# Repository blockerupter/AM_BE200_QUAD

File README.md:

AM_BE200_QUAD
=============

BE200 Board with 4 chips

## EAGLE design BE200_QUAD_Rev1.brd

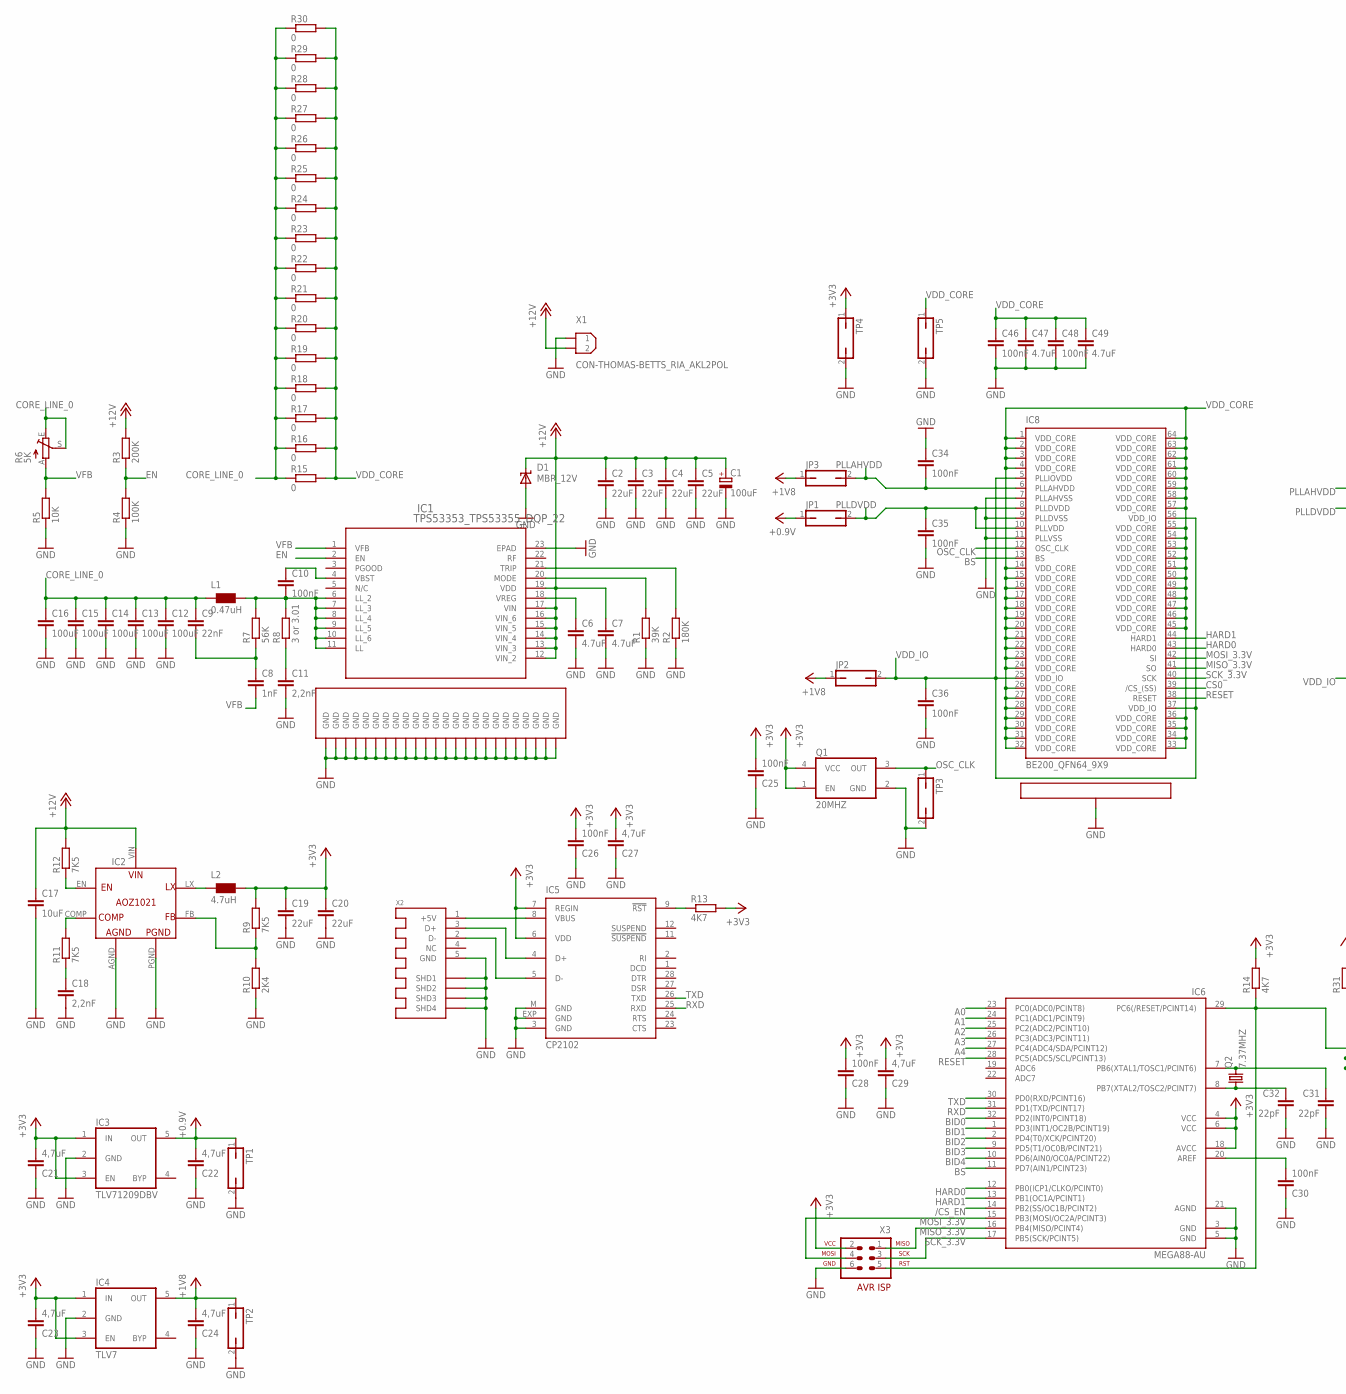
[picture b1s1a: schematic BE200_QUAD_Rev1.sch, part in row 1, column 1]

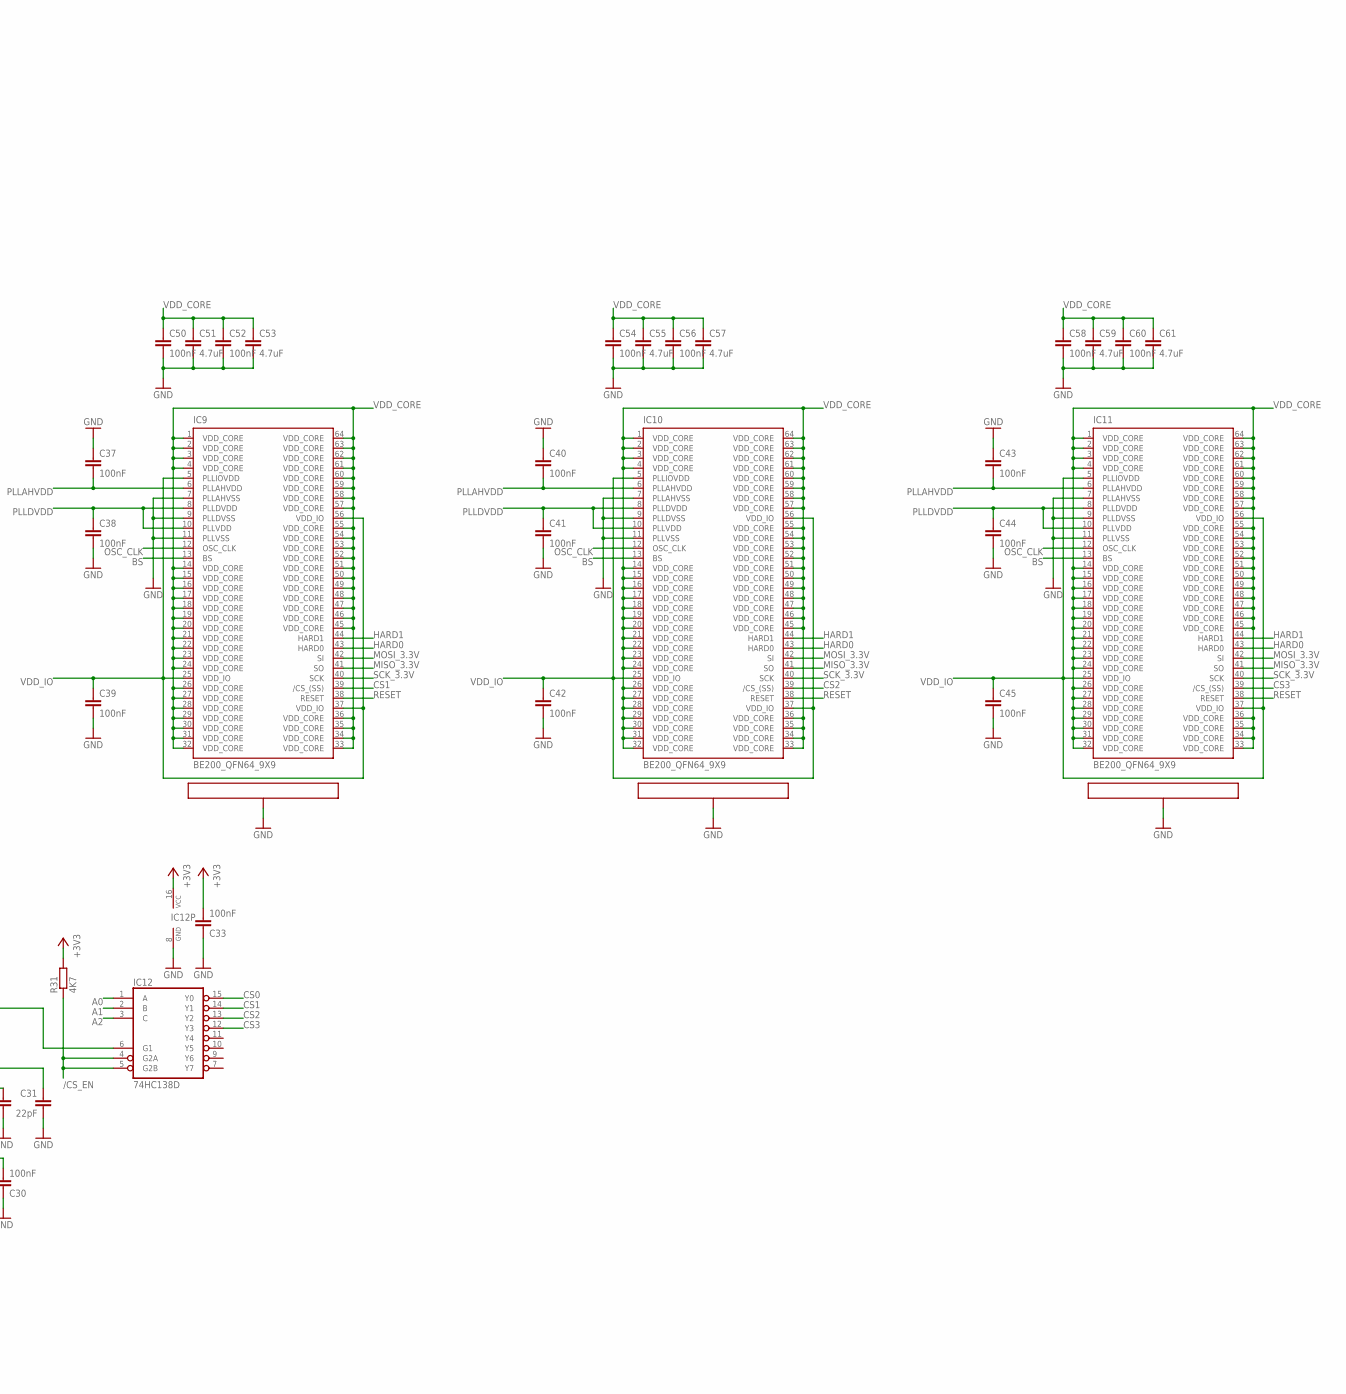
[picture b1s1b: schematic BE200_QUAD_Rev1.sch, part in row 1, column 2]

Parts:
C1: 100uF; 153CLV-0605
C2, C3, C4, C5: 22uF; C1210K
C6, C7: 4.7uF; C0805K
C8: 1nF; C0805K
C9: 22nF; C0805K
C10, C25, C26, C28, C30, C33: 100nF; C0805K
C11, C18: 2,2nF; C0805K
C12, C13, C14, C15, C16: 100uF; C1210K
C17: 10uF; C1206K
C19, C20: 22uF; C1206K
C21, C22, C23, C24, C27, C29: 4,7uF; C0805K
C31, C32: 22pF; C0805K
C34, C35, C36, C37, C38, C39, C40, C41, C42, C43, C44, C45, C46, C48, C50, C52, C54, C56, C58, C60: 100nF; MYRCL_C0603K
C47, C49, C51, C53, C55, C57, C59, C61: 4.7uF; MYRCL_C0603K
D1: MBR_12V; SMBJ
IC1: TPS53353_TPS53355_DQP_22; DQP22_5P479X3P24
IC2: AOZ1021
IC3: TLV71209DBV; SOT-23-5
IC4: TLV7; SOT-23-5
IC5: CP2102; SILABS2_MLP28
IC6: MEGA88-AU; TQFP32-08
IC8, IC9, IC10, IC11: BE200_QFN64_9X9; QFN64-9X9
IC12: 74HC138D; SO16
JP1, JP2, JP3: JP1Q; JP1
L1: 0.47uH; INDUCTOR_PA0513
L2: 4.7uH; INDCUCTOR_7.3X7.3
Q1: 20MHZ; OSCILLATOR_7X5_SMD
Q2: 7.37MHZ; HC49UP
R1: 39K; R0805K
R2: 180K; R0805K
R3: 200K; R0805K
R4: 100K; R0805K
R5: 10K; R0805K
R6: 5K; S64W
R7: 56K; R0805K
R8: 3 or 3.01; R0805K
R9, R11, R12: 7K5; R0805K
R10: 2K4; R0805K
R13, R14, R31: 4K7; R0805K
R15, R16, R17, R18, R19, R20, R21, R22, R23, R24, R25, R26, R27, R28, R29, R30: 0; R0805K
TP1, TP2, TP3, TP4, TP5: JP1Q; JP1
X1: CON-THOMAS-BETTS_RIA_AKL2POL
X2: MYSTUFF_USB-MINI-ASSMANN; MYSTUFF_USB_MINI-ASSMANN
X3: AVR-ISP-6VERT; AVR-ISP-6

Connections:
+0.9V: C22.2, IC3.5 (OUT), JP1.1, TP1.1
+1V8: C24.2, IC4.5 (OUT), JP2.1, JP3.1, TP2.1
+3V3: C19.1, C20.1, C21.2, C23.2, C25.2, C26.2, C27.2, C28.2, C29.2, C33.2, IC3.1 (IN), IC3.3 (EN), IC4.1 (IN), IC4.3 (EN), IC5.6 (VDD), IC5.7 (REGIN), IC6.4 (VCC), IC6.6 (VCC), IC6.18 (AVCC), IC12.16 (VCC), L2.2, Q1.1 (EN), Q1.4 (VCC), R9.2, R13.2, R14.2, R31.2, TP4.1, X3.2
+12V: C1.+, C2.1, C3.1, C4.1, C5.1, C7.1, C17.1, D1.C, IC1.12 (VIN_2), IC1.13 (VIN_3), IC1.14 (VIN_4), IC1.15 (VIN_5), IC1.16 (VIN_6), IC1.17 (VIN), IC1.19 (VDD), IC2.VIN, R3.2, R12.2, X1.2
/CS_EN: IC6.14 (PB2(SS/OC1B/PCINT2)), IC12.4 (G2A), IC12.5 (G2B), R31.1
A0: IC6.23 (PC0(ADC0/PCINT8)), IC12.1 (A)
A1: IC6.24 (PC1(ADC1/PCINT9)), IC12.2 (B)
A2: IC6.25 (PC2(ADC2/PCINT10)), IC12.3 (C)
A3: IC6.26 (PC3(ADC3/PCINT11))
A4: IC6.27 (PC4(ADC4/SDA/PCINT12))
BID0: IC6.32 (PD2(INT0/PCINT18))
BID1: IC6.1 (PD3(INT1/OC2B/PCINT19))
BID2: IC6.2 (PD4(T0/XCK/PCINT20))
BID3: IC6.9 (PD5(T1/OC0B/PCINT21))
BID4: IC6.10 (PD6(AIN0/OC0A/PCINT22))
BS: IC6.11 (PD7(AIN1/PCINT23)), IC8.13 (BS), IC9.13 (BS), IC10.13 (BS), IC11.13 (BS)
CORE_LINE_0: C9.1, C12.1, C13.1, C14.1, C15.1, C16.1, L1.1, R6.E, R6.S, R15.1, R16.1, R17.1, R18.1, R19.1, R20.1, R21.1, R22.1, R23.1, R24.1, R25.1, R26.1, R27.1, R28.1, R29.1, R30.1
CS0: IC8.39 (/CS_(SS)), IC12.15 (Y0)
CS1: IC9.39 (/CS_(SS)), IC12.14 (Y1)
CS2: IC10.39 (/CS_(SS)), IC12.13 (Y2)
CS3: IC11.39 (/CS_(SS)), IC12.12 (Y3)
EN: IC1.2 (EN), R3.1, R4.2
GND: C1.-, C2.2, C3.2, C4.2, C5.2, C6.2, C7.2, C11.2, C12.2, C13.2, C14.2, C15.2, C16.2, C17.2, C18.2, C19.2, C20.2, C21.1, C22.1, C23.1, C24.1, C25.1, C26.1, C27.1, C28.1, C29.1, C30.1, C31.2, C32.2, C33.1, C34.1, C35.2, C36.2, C37.1, C38.2, C39.2, C40.1, C41.2, C42.2, C43.1, C44.2, C45.2, C46.2, C47.2, C48.2, C49.2, C50.2, C51.2, C52.2, C53.2, C54.2, C55.2, C56.2, C57.2, C58.2, C59.2, C60.2, C61.2, D1.A, IC1.23 (EPAD), IC1.GND@1 (GND), IC1.GND@2 (GND), IC1.GND@3 (GND), IC1.GND@4 (GND), IC1.GND@5 (GND), IC1.GND@6 (GND), IC1.GND@7 (GND), IC1.GND@8 (GND), IC1.GND@9 (GND), IC1.GND@10 (GND), IC1.GND@11 (GND), IC1.GND@12 (GND), IC1.GND@13 (GND), IC1.GND@14 (GND), IC1.GND@15 (GND), IC1.GND@16 (GND), IC1.GND@17 (GND), IC1.GND@18 (GND), IC1.GND@19 (GND), IC1.GND@20 (GND), IC1.GND@21 (GND), IC1.GND@22 (GND), IC1.GND@23 (GND), IC1.GND@24 (GND), IC2.AGND, IC2.PGND, IC3.2 (GND), IC4.2 (GND), IC5.3 (GND), IC5.EXP (GND), IC5.M (GND), IC6.3 (GND), IC6.5 (GND), IC6.21 (AGND), IC8.7 (PLLAHVSS), IC8.9 (PLLDVSS), IC8.11 (PLLVSS), IC8.EXP@1 (GND), IC8.EXP@2 (GND), IC8.EXP@3 (GND), IC8.EXP@4 (GND), IC8.EXP@5 (GND), IC8.EXP@6 (GND), IC8.EXP@7 (GND), IC8.EXP@8 (GND), IC8.EXP@9 (GND), IC8.EXP@10 (GND), IC8.EXP@11 (GND), IC8.EXP@12 (GND), IC8.EXP@13 (GND), IC8.EXP@14 (GND), IC8.EXP@15 (GND), IC8.EXP@16 (GND), IC8.EXP@17 (GND), IC8.EXP@18 (GND), IC8.EXP@19 (GND), IC8.EXP@20 (GND), IC8.EXP@21 (GND), IC8.EXP@22 (GND), IC8.EXP@23 (GND), IC8.EXP@24 (GND), IC8.EXP@25 (GND), IC8.EXP@26 (GND), IC8.EXP@27 (GND), IC8.EXP@28 (GND), IC8.EXP@29 (GND), IC8.EXP@30 (GND), IC8.EXP@31 (GND), IC8.EXP@32 (GND), IC8.EXP@33 (GND), IC8.EXP@34 (GND), IC8.EXP@35 (GND), IC8.EXP@36 (GND), IC8.EXP@37 (GND), IC8.EXP@38 (GND), IC8.EXP@39 (GND), IC8.EXP@40 (GND), IC8.EXP@41 (GND), IC8.EXP@42 (GND), IC8.EXP@43 (GND), IC8.EXP@44 (GND), IC8.EXP@45 (GND), IC8.EXP@46 (GND), IC8.EXP@47 (GND), IC8.EXP@48 (GND), IC8.EXP@49 (GND), IC9.7 (PLLAHVSS), IC9.9 (PLLDVSS), IC9.11 (PLLVSS), IC9.EXP@1 (GND), IC9.EXP@2 (GND), IC9.EXP@3 (GND), IC9.EXP@4 (GND), IC9.EXP@5 (GND), IC9.EXP@6 (GND), IC9.EXP@7 (GND), IC9.EXP@8 (GND), IC9.EXP@9 (GND), IC9.EXP@10 (GND), IC9.EXP@11 (GND), IC9.EXP@12 (GND), IC9.EXP@13 (GND), IC9.EXP@14 (GND), IC9.EXP@15 (GND), IC9.EXP@16 (GND), IC9.EXP@17 (GND), IC9.EXP@18 (GND), IC9.EXP@19 (GND), IC9.EXP@20 (GND), IC9.EXP@21 (GND), IC9.EXP@22 (GND), IC9.EXP@23 (GND), IC9.EXP@24 (GND), IC9.EXP@25 (GND), IC9.EXP@26 (GND), IC9.EXP@27 (GND), IC9.EXP@28 (GND), IC9.EXP@29 (GND), IC9.EXP@30 (GND), IC9.EXP@31 (GND), IC9.EXP@32 (GND), IC9.EXP@33 (GND), IC9.EXP@34 (GND), IC9.EXP@35 (GND), IC9.EXP@36 (GND), IC9.EXP@37 (GND), IC9.EXP@38 (GND), IC9.EXP@39 (GND), IC9.EXP@40 (GND), IC9.EXP@41 (GND), IC9.EXP@42 (GND), IC9.EXP@43 (GND), IC9.EXP@44 (GND), IC9.EXP@45 (GND), IC9.EXP@46 (GND), IC9.EXP@47 (GND), IC9.EXP@48 (GND), IC9.EXP@49 (GND), IC10.7 (PLLAHVSS), IC10.9 (PLLDVSS), IC10.11 (PLLVSS), IC10.EXP@1 (GND), IC10.EXP@2 (GND), IC10.EXP@3 (GND), IC10.EXP@4 (GND), IC10.EXP@5 (GND), IC10.EXP@6 (GND), IC10.EXP@7 (GND), IC10.EXP@8 (GND), IC10.EXP@9 (GND), IC10.EXP@10 (GND), IC10.EXP@11 (GND), IC10.EXP@12 (GND), IC10.EXP@13 (GND), IC10.EXP@14 (GND), IC10.EXP@15 (GND), IC10.EXP@16 (GND), IC10.EXP@17 (GND), IC10.EXP@18 (GND), IC10.EXP@19 (GND), IC10.EXP@20 (GND), IC10.EXP@21 (GND), IC10.EXP@22 (GND), IC10.EXP@23 (GND), IC10.EXP@24 (GND), IC10.EXP@25 (GND), IC10.EXP@26 (GND), IC10.EXP@27 (GND), IC10.EXP@28 (GND), IC10.EXP@29 (GND), IC10.EXP@30 (GND), IC10.EXP@31 (GND), IC10.EXP@32 (GND), IC10.EXP@33 (GND), IC10.EXP@34 (GND), IC10.EXP@35 (GND), IC10.EXP@36 (GND), IC10.EXP@37 (GND), IC10.EXP@38 (GND), IC10.EXP@39 (GND), IC10.EXP@40 (GND), IC10.EXP@41 (GND), IC10.EXP@42 (GND), IC10.EXP@43 (GND), IC10.EXP@44 (GND), IC10.EXP@45 (GND), IC10.EXP@46 (GND), IC10.EXP@47 (GND), IC10.EXP@48 (GND), IC10.EXP@49 (GND), IC11.7 (PLLAHVSS), IC11.9 (PLLDVSS), IC11.11 (PLLVSS), IC11.EXP@1 (GND), IC11.EXP@2 (GND), IC11.EXP@3 (GND), IC11.EXP@4 (GND), IC11.EXP@5 (GND), IC11.EXP@6 (GND), IC11.EXP@7 (GND), IC11.EXP@8 (GND), IC11.EXP@9 (GND), IC11.EXP@10 (GND), IC11.EXP@11 (GND), IC11.EXP@12 (GND), IC11.EXP@13 (GND), IC11.EXP@14 (GND), IC11.EXP@15 (GND), IC11.EXP@16 (GND), IC11.EXP@17 (GND), IC11.EXP@18 (GND), IC11.EXP@19 (GND), IC11.EXP@20 (GND), IC11.EXP@21 (GND), IC11.EXP@22 (GND), IC11.EXP@23 (GND), IC11.EXP@24 (GND), IC11.EXP@25 (GND), IC11.EXP@26 (GND), IC11.EXP@27 (GND), IC11.EXP@28 (GND), IC11.EXP@29 (GND), IC11.EXP@30 (GND), IC11.EXP@31 (GND), IC11.EXP@32 (GND), IC11.EXP@33 (GND), IC11.EXP@34 (GND), IC11.EXP@35 (GND), IC11.EXP@36 (GND), IC11.EXP@37 (GND), IC11.EXP@38 (GND), IC11.EXP@39 (GND), IC11.EXP@40 (GND), IC11.EXP@41 (GND), IC11.EXP@42 (GND), IC11.EXP@43 (GND), IC11.EXP@44 (GND), IC11.EXP@45 (GND), IC11.EXP@46 (GND), IC11.EXP@47 (GND), IC11.EXP@48 (GND), IC11.EXP@49 (GND), IC12.8 (GND), Q1.2 (GND), R1.1, R2.1, R4.1, R5.1, R10.1, TP1.2, TP2.2, TP3.2, TP4.2, TP5.2, X1.1, X2.5 (GND), X2.SHD1, X2.SHD2, X2.SHD3, X2.SHD4, X3.6
HARD0: IC6.12 (PB0(ICP1/CLKO/PCINT0)), IC8.43 (HARD0), IC9.43 (HARD0), IC10.43 (HARD0), IC11.43 (HARD0)
HARD1: IC6.13 (PB1(OC1A/PCINT1)), IC8.44 (HARD1), IC9.44 (HARD1), IC10.44 (HARD1), IC11.44 (HARD1)
MISO_3.3V: IC6.16 (PB4(MISO/PCINT4)), IC8.41 (SO), IC9.41 (SO), IC10.41 (SO), IC11.41 (SO), X3.1
MOSI_3.3V: IC6.15 (PB3(MOSI/OC2A/PCINT3)), IC8.42 (SI), IC9.42 (SI), IC10.42 (SI), IC11.42 (SI), X3.4
unnamed: C10.2, IC1.6 (LL_2), IC1.7 (LL_3), IC1.8 (LL_4), IC1.9 (LL_5), IC1.10 (LL_6), IC1.11 (LL), L1.2, R7.2, R8.2
unnamed: C11.1, R8.1
unnamed: C8.1, C9.2, R7.1
unnamed: IC6.29 (PC6(/RESET/PCINT14)), IC12.6 (G1), R14.1, X3.5
unnamed: IC1.21 (TRIP), R2.2
unnamed: IC1.20 (MODE), R1.2
unnamed: C6.1, IC1.18 (VREG)
unnamed: C10.1, IC1.4 (VBST)
unnamed: C18.1, R11.1
unnamed: IC2.LX, L2.1
unnamed: IC2.FB, R9.1, R10.2
unnamed: IC2.COMP, R11.2
unnamed: IC2.EN, R12.1
unnamed: C30.2, IC6.20 (AREF)
unnamed: C31.1, IC6.7 (PB6(XTAL1/TOSC1/PCINT6)), Q2.2
unnamed: IC5.9 (!RST), R13.1
unnamed: C32.1, IC6.8 (PB7(XTAL2/TOSC2/PCINT7)), Q2.1
unnamed: IC5.4 (D+), X2.3 (D+)
unnamed: IC5.5 (D-), X2.2 (D-)
unnamed: IC5.8 (VBUS), X2.1 (+5V)
OSC_CLK: IC8.12 (OSC_CLK), IC9.12 (OSC_CLK), IC10.12 (OSC_CLK), IC11.12 (OSC_CLK), Q1.3 (OUT), TP3.1
PLLAHVDD: C34.2, C37.2, C40.2, C43.2, IC8.6 (PLLAHVDD), IC9.6 (PLLAHVDD), IC10.6 (PLLAHVDD), IC11.6 (PLLAHVDD), JP3.2
PLLDVDD: C35.1, C38.1, C41.1, C44.1, IC8.8 (PLLDVDD), IC8.10 (PLLVDD), IC9.8 (PLLDVDD), IC9.10 (PLLVDD), IC10.8 (PLLDVDD), IC10.10 (PLLVDD), IC11.8 (PLLDVDD), IC11.10 (PLLVDD), JP1.2
RESET: IC6.28 (PC5(ADC5/SCL/PCINT13)), IC8.38 (RESET), IC9.38 (RESET), IC10.38 (RESET), IC11.38 (RESET)
RXD: IC5.25 (RXD), IC6.31 (PD1(TXD/PCINT17))
SCK_3.3V: IC6.17 (PB5(SCK/PCINT5)), IC8.40 (SCK), IC9.40 (SCK), IC10.40 (SCK), IC11.40 (SCK), X3.3
TXD: IC5.26 (TXD), IC6.30 (PD0(RXD/PCINT16))
VDD_CORE: C46.1, C47.1, C48.1, C49.1, C50.1, C51.1, C52.1, C53.1, C54.1, C55.1, C56.1, C57.1, C58.1, C59.1, C60.1, C61.1, IC8.1 (VDD_CORE), IC8.2 (VDD_CORE), IC8.3 (VDD_CORE), IC8.4 (VDD_CORE), IC8.14 (VDD_CORE), IC8.15 (VDD_CORE), IC8.16 (VDD_CORE), IC8.17 (VDD_CORE), IC8.18 (VDD_CORE), IC8.19 (VDD_CORE), IC8.20 (VDD_CORE), IC8.21 (VDD_CORE), IC8.22 (VDD_CORE), IC8.23 (VDD_CORE), IC8.24 (VDD_CORE), IC8.26 (VDD_CORE), IC8.27 (VDD_CORE), IC8.28 (VDD_CORE), IC8.29 (VDD_CORE), IC8.30 (VDD_CORE), IC8.31 (VDD_CORE), IC8.32 (VDD_CORE), IC8.33 (VDD_CORE), IC8.34 (VDD_CORE), IC8.35 (VDD_CORE), IC8.36 (VDD_CORE), IC8.45 (VDD_CORE), IC8.46 (VDD_CORE), IC8.47 (VDD_CORE), IC8.48 (VDD_CORE), IC8.49 (VDD_CORE), IC8.50 (VDD_CORE), IC8.51 (VDD_CORE), IC8.52 (VDD_CORE), IC8.53 (VDD_CORE), IC8.54 (VDD_CORE), IC8.55 (VDD_CORE), IC8.57 (VDD_CORE), IC8.58 (VDD_CORE), IC8.59 (VDD_CORE), IC8.60 (VDD_CORE), IC8.61 (VDD_CORE), IC8.62 (VDD_CORE), IC8.63 (VDD_CORE), IC8.64 (VDD_CORE), IC9.1 (VDD_CORE), IC9.2 (VDD_CORE), IC9.3 (VDD_CORE), IC9.4 (VDD_CORE), IC9.14 (VDD_CORE), IC9.15 (VDD_CORE), IC9.16 (VDD_CORE), IC9.17 (VDD_CORE), IC9.18 (VDD_CORE), IC9.19 (VDD_CORE), IC9.20 (VDD_CORE), IC9.21 (VDD_CORE), IC9.22 (VDD_CORE), IC9.23 (VDD_CORE), IC9.24 (VDD_CORE), IC9.26 (VDD_CORE), IC9.27 (VDD_CORE), IC9.28 (VDD_CORE), IC9.29 (VDD_CORE), IC9.30 (VDD_CORE), IC9.31 (VDD_CORE), IC9.32 (VDD_CORE), IC9.33 (VDD_CORE), IC9.34 (VDD_CORE), IC9.35 (VDD_CORE), IC9.36 (VDD_CORE), IC9.45 (VDD_CORE), IC9.46 (VDD_CORE), IC9.47 (VDD_CORE), IC9.48 (VDD_CORE), IC9.49 (VDD_CORE), IC9.50 (VDD_CORE), IC9.51 (VDD_CORE), IC9.52 (VDD_CORE), IC9.53 (VDD_CORE), IC9.54 (VDD_CORE), IC9.55 (VDD_CORE), IC9.57 (VDD_CORE), IC9.58 (VDD_CORE), IC9.59 (VDD_CORE), IC9.60 (VDD_CORE), IC9.61 (VDD_CORE), IC9.62 (VDD_CORE), IC9.63 (VDD_CORE), IC9.64 (VDD_CORE), IC10.1 (VDD_CORE), IC10.2 (VDD_CORE), IC10.3 (VDD_CORE), IC10.4 (VDD_CORE), IC10.14 (VDD_CORE), IC10.15 (VDD_CORE), IC10.16 (VDD_CORE), IC10.17 (VDD_CORE), IC10.18 (VDD_CORE), IC10.19 (VDD_CORE), IC10.20 (VDD_CORE), IC10.21 (VDD_CORE), IC10.22 (VDD_CORE), IC10.23 (VDD_CORE), IC10.24 (VDD_CORE), IC10.26 (VDD_CORE), IC10.27 (VDD_CORE), IC10.28 (VDD_CORE), IC10.29 (VDD_CORE), IC10.30 (VDD_CORE), IC10.31 (VDD_CORE), IC10.32 (VDD_CORE), IC10.33 (VDD_CORE), IC10.34 (VDD_CORE), IC10.35 (VDD_CORE), IC10.36 (VDD_CORE), IC10.45 (VDD_CORE), IC10.46 (VDD_CORE), IC10.47 (VDD_CORE), IC10.48 (VDD_CORE), IC10.49 (VDD_CORE), IC10.50 (VDD_CORE), IC10.51 (VDD_CORE), IC10.52 (VDD_CORE), IC10.53 (VDD_CORE), IC10.54 (VDD_CORE), IC10.55 (VDD_CORE), IC10.57 (VDD_CORE), IC10.58 (VDD_CORE), IC10.59 (VDD_CORE), IC10.60 (VDD_CORE), IC10.61 (VDD_CORE), IC10.62 (VDD_CORE), IC10.63 (VDD_CORE), IC10.64 (VDD_CORE), IC11.1 (VDD_CORE), IC11.2 (VDD_CORE), IC11.3 (VDD_CORE), IC11.4 (VDD_CORE), IC11.14 (VDD_CORE), IC11.15 (VDD_CORE), IC11.16 (VDD_CORE), IC11.17 (VDD_CORE), IC11.18 (VDD_CORE), IC11.19 (VDD_CORE), IC11.20 (VDD_CORE), IC11.21 (VDD_CORE), IC11.22 (VDD_CORE), IC11.23 (VDD_CORE), IC11.24 (VDD_CORE), IC11.26 (VDD_CORE), IC11.27 (VDD_CORE), IC11.28 (VDD_CORE), IC11.29 (VDD_CORE), IC11.30 (VDD_CORE), IC11.31 (VDD_CORE), IC11.32 (VDD_CORE), IC11.33 (VDD_CORE), IC11.34 (VDD_CORE), IC11.35 (VDD_CORE), IC11.36 (VDD_CORE), IC11.45 (VDD_CORE), IC11.46 (VDD_CORE), IC11.47 (VDD_CORE), IC11.48 (VDD_CORE), IC11.49 (VDD_CORE), IC11.50 (VDD_CORE), IC11.51 (VDD_CORE), IC11.52 (VDD_CORE), IC11.53 (VDD_CORE), IC11.54 (VDD_CORE), IC11.55 (VDD_CORE), IC11.57 (VDD_CORE), IC11.58 (VDD_CORE), IC11.59 (VDD_CORE), IC11.60 (VDD_CORE), IC11.61 (VDD_CORE), IC11.62 (VDD_CORE), IC11.63 (VDD_CORE), IC11.64 (VDD_CORE), R15.2, R16.2, R17.2, R18.2, R19.2, R20.2, R21.2, R22.2, R23.2, R24.2, R25.2, R26.2, R27.2, R28.2, R29.2, R30.2, TP5.1
VDD_IO: C36.1, C39.1, C42.1, C45.1, IC8.5 (PLLIOVDD), IC8.25 (VDD_IO), IC8.37 (VDD_IO), IC8.56 (VDD_IO), IC9.5 (PLLIOVDD), IC9.25 (VDD_IO), IC9.37 (VDD_IO), IC9.56 (VDD_IO), IC10.5 (PLLIOVDD), IC10.25 (VDD_IO), IC10.37 (VDD_IO), IC10.56 (VDD_IO), IC11.5 (PLLIOVDD), IC11.25 (VDD_IO), IC11.37 (VDD_IO), IC11.56 (VDD_IO), JP2.2
VFB: C8.2, IC1.1 (VFB), R5.2, R6.A

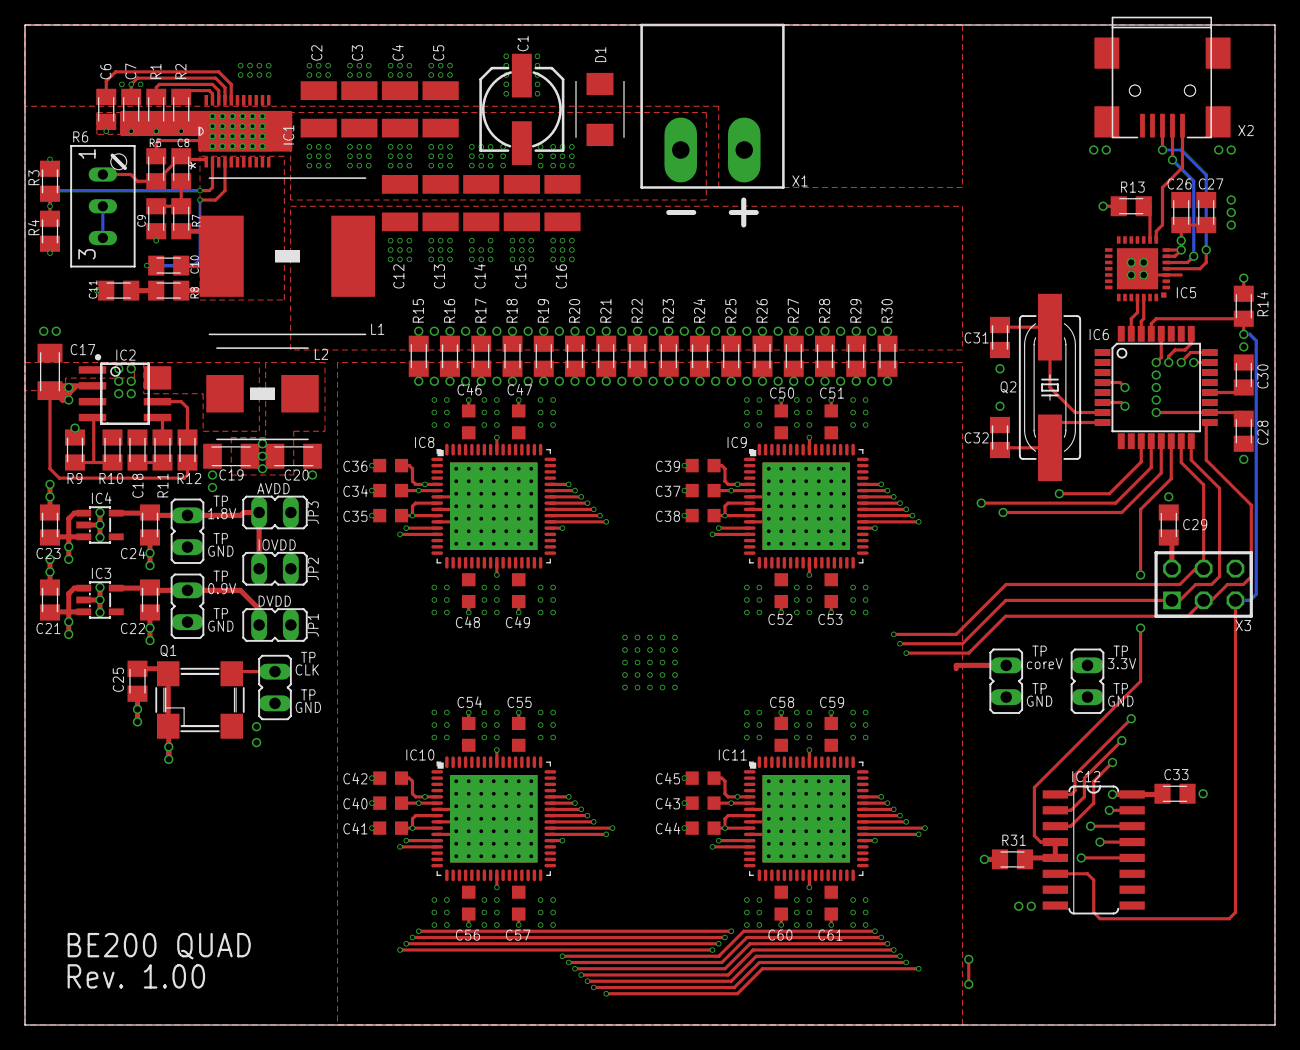
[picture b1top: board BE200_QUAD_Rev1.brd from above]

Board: 4 copper layers, 100.0 x 80.0 mm, 119 parts (0 on the bottom side), 50 nets.

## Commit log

2014-06-06 Rev 1 Quad Chip Hashing Board
2014-06-14 Add BOM
